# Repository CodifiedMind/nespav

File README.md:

# nespav
A simple replacement for the NES RF/power module providing composite video and mono audio output. Uses the nifty little Recom R-78K-2.0 switching mode power supply module to simplify the design.

_Composite video amplifier circuit is based on Merlin Shaw's design (https://github.com/ShawMerlin/NES-Power-Module-Redesign)._

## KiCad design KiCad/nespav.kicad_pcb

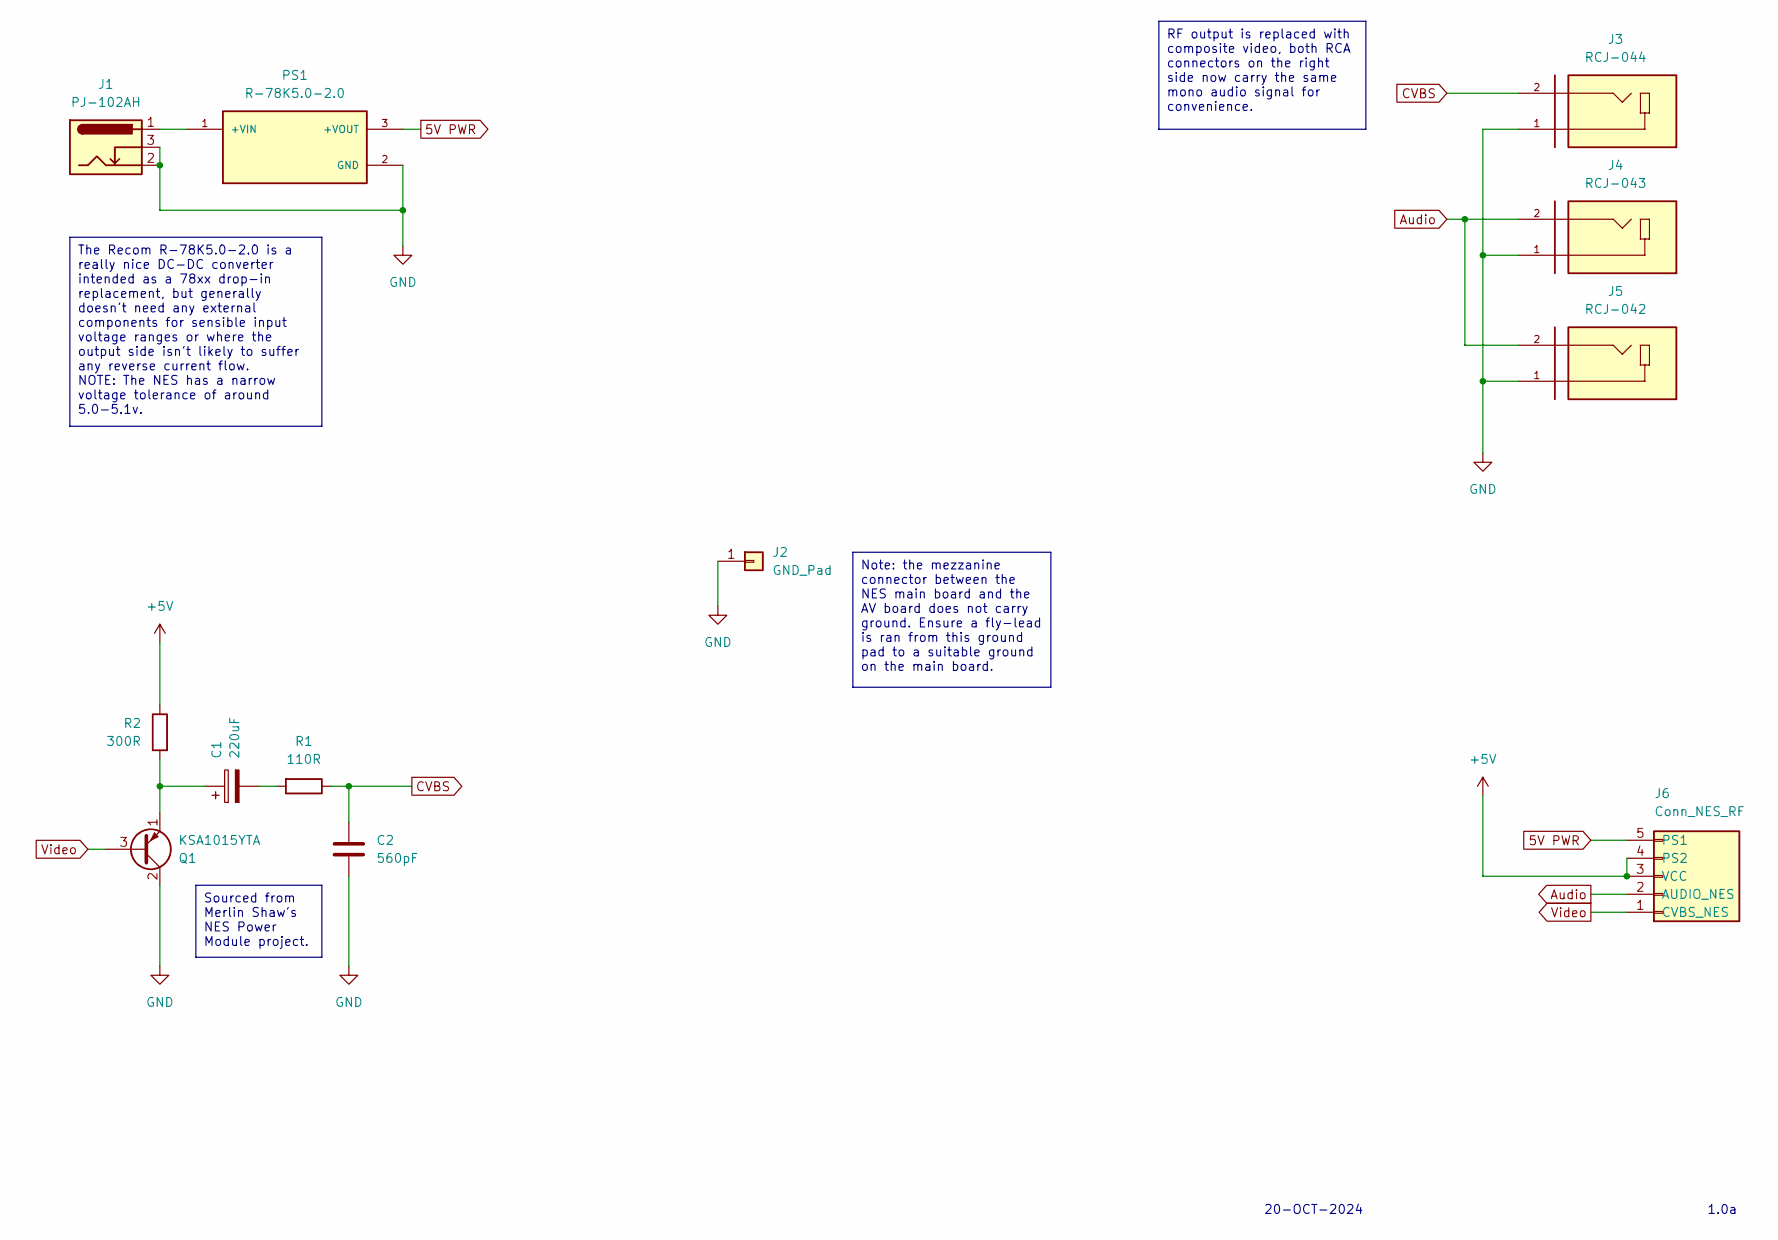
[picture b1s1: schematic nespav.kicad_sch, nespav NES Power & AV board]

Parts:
C1: 220uF; CP_Radial_D6.3mm_P2.50mm
C2: 560pF; C_Disc_D4.7mm_W2.5mm_P5.00mm
J1: PJ-102AH; BarrelJack_CUI_PJ-102AH_Horizontal
J2: GND_Pad; Pin_D1.3mm_L11.0mm
J3: RCJ-044; CUI_RCJ-044; PARTREV 1.02
J4: RCJ-043; CUI_RCJ-044; PARTREV 1.02
J5: RCJ-042; CUI_RCJ-044; PARTREV 1.02
J6: Conn_NES_RF; RF_CONN_NES
PS1: R-78K5.0-2.0; CONV_R-78K5.0-2.0; PARTREV 0/2023
Q1: KSA1015YTA; TO-92L_Inline_Wide
R1: 110R; R_Axial_DIN0207_L6.3mm_D2.5mm_P10.16mm_Horizontal
R2: 300R; R_Axial_DIN0207_L6.3mm_D2.5mm_P10.16mm_Horizontal

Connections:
5V PWR: J6.5 (PS1), PS1.3 (+VOUT)
+5V: J6.3 (VCC), J6.4 (PS2), R2.1
Audio: J4.2, J5.2, J6.2 (AUDIO_NES)
CVBS: C2.1, J3.2, R1.1
GND: C2.2, J1.2, J1.3, J2.1, J3.1, J4.1, J5.1, PS1.2 (GND), Q1.2 (C)
unnamed: C1.2, R1.2
unnamed: J1.1, PS1.1 (+VIN)
unnamed: C1.1, Q1.1 (E), R2.2
Video: J6.1 (CVBS_NES), Q1.3 (B)

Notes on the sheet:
Note: the mezzanine connector between the NES main board and the AV board does not carry ground. Ensure a fly-lead is ran from this ground pad to a suitable ground on the main board.
RF output is replaced with composite video, both RCA connectors on the right side now carry the same mono audio signal for convenience.
The Recom R-78K5.0-2.0 is a really nice DC-DC converter intended as a 78xx drop-in replacement, but generally doesn't need any external components for sensible input voltage ranges or where the output side isn't likely to suffer any reverse current flow. NOTE: The NES has a narrow voltage tolerance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
Sourced from Merlin Shaw's NES Power Module project.
20-OCT-2024
1.0a

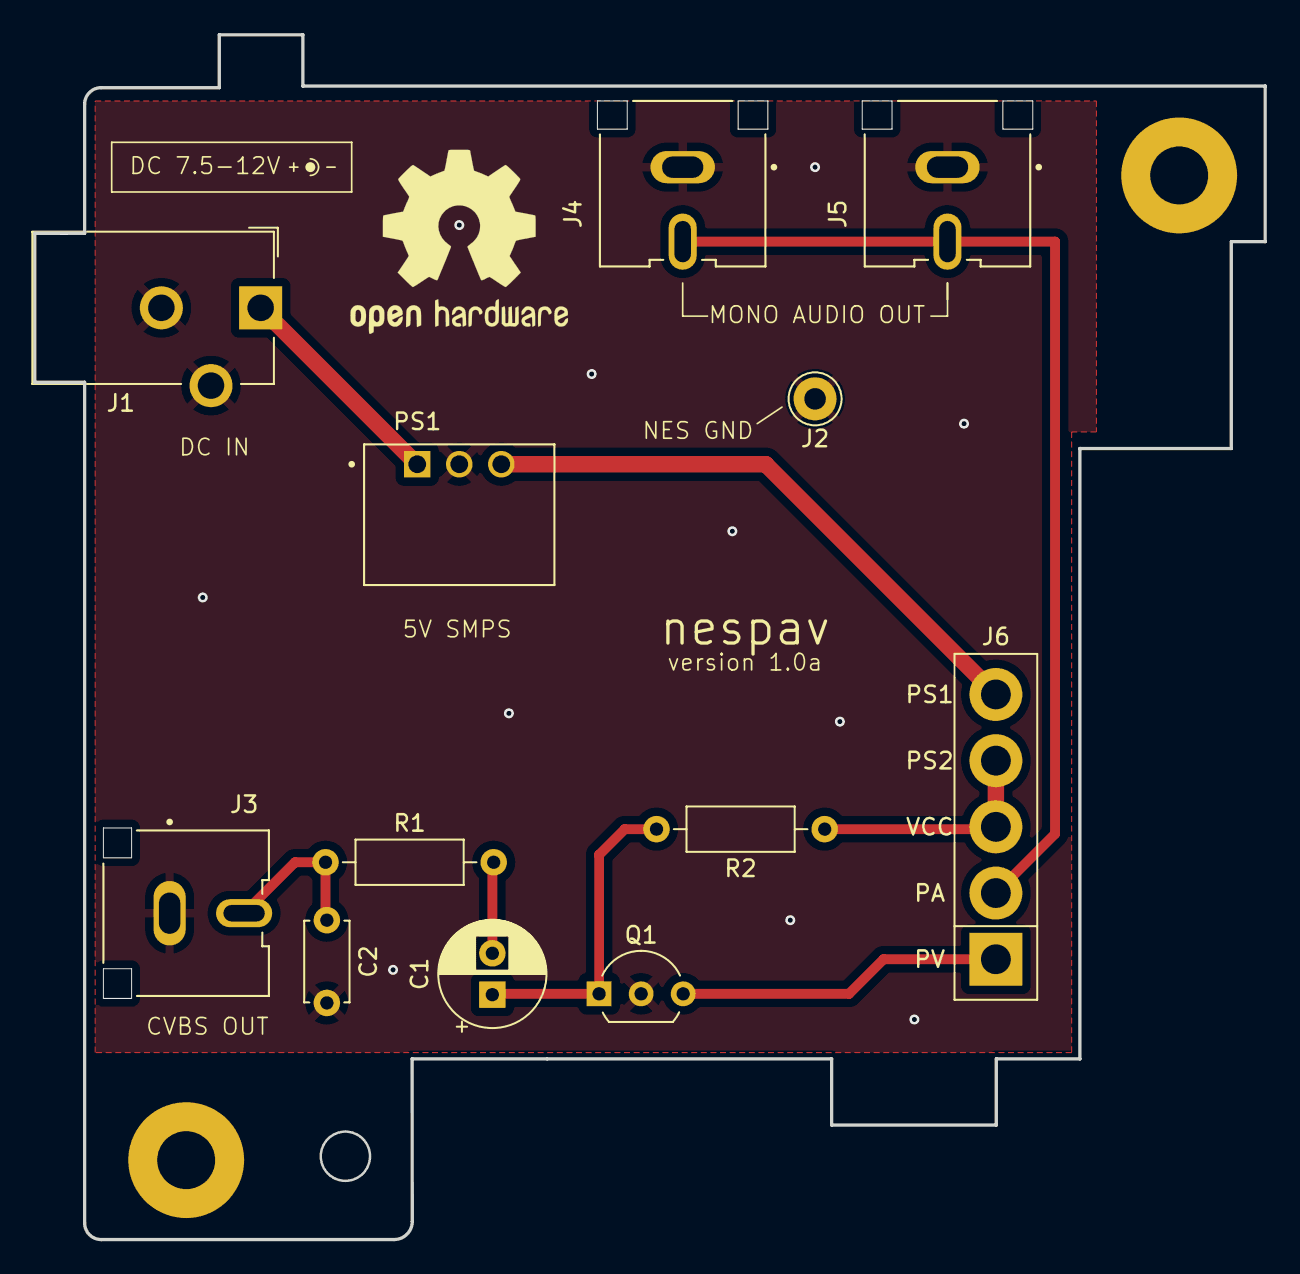
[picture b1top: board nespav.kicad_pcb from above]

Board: 2 copper layers, 74.3 x 72.8 mm, 12 parts (0 on the bottom side), 9 nets.

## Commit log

2024-11-04 First commit of KiCad files
